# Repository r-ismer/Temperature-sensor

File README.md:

# Temperature sensor

This folder contains a hardware, a software part and a mechanical part.  
The hardware part is a KiCad project which contains the schematic and the pcb layout for the temperature and humidity sensor.  
The software part is a make project which contains all the files needed to build the firwmare that will communicate with the temperature and humidity sensor and send these inforamtion to a station (other project).  
The mechanical part is a FreeCAD project which contains the top and bottom casing for the temperature ad humidity sensor.

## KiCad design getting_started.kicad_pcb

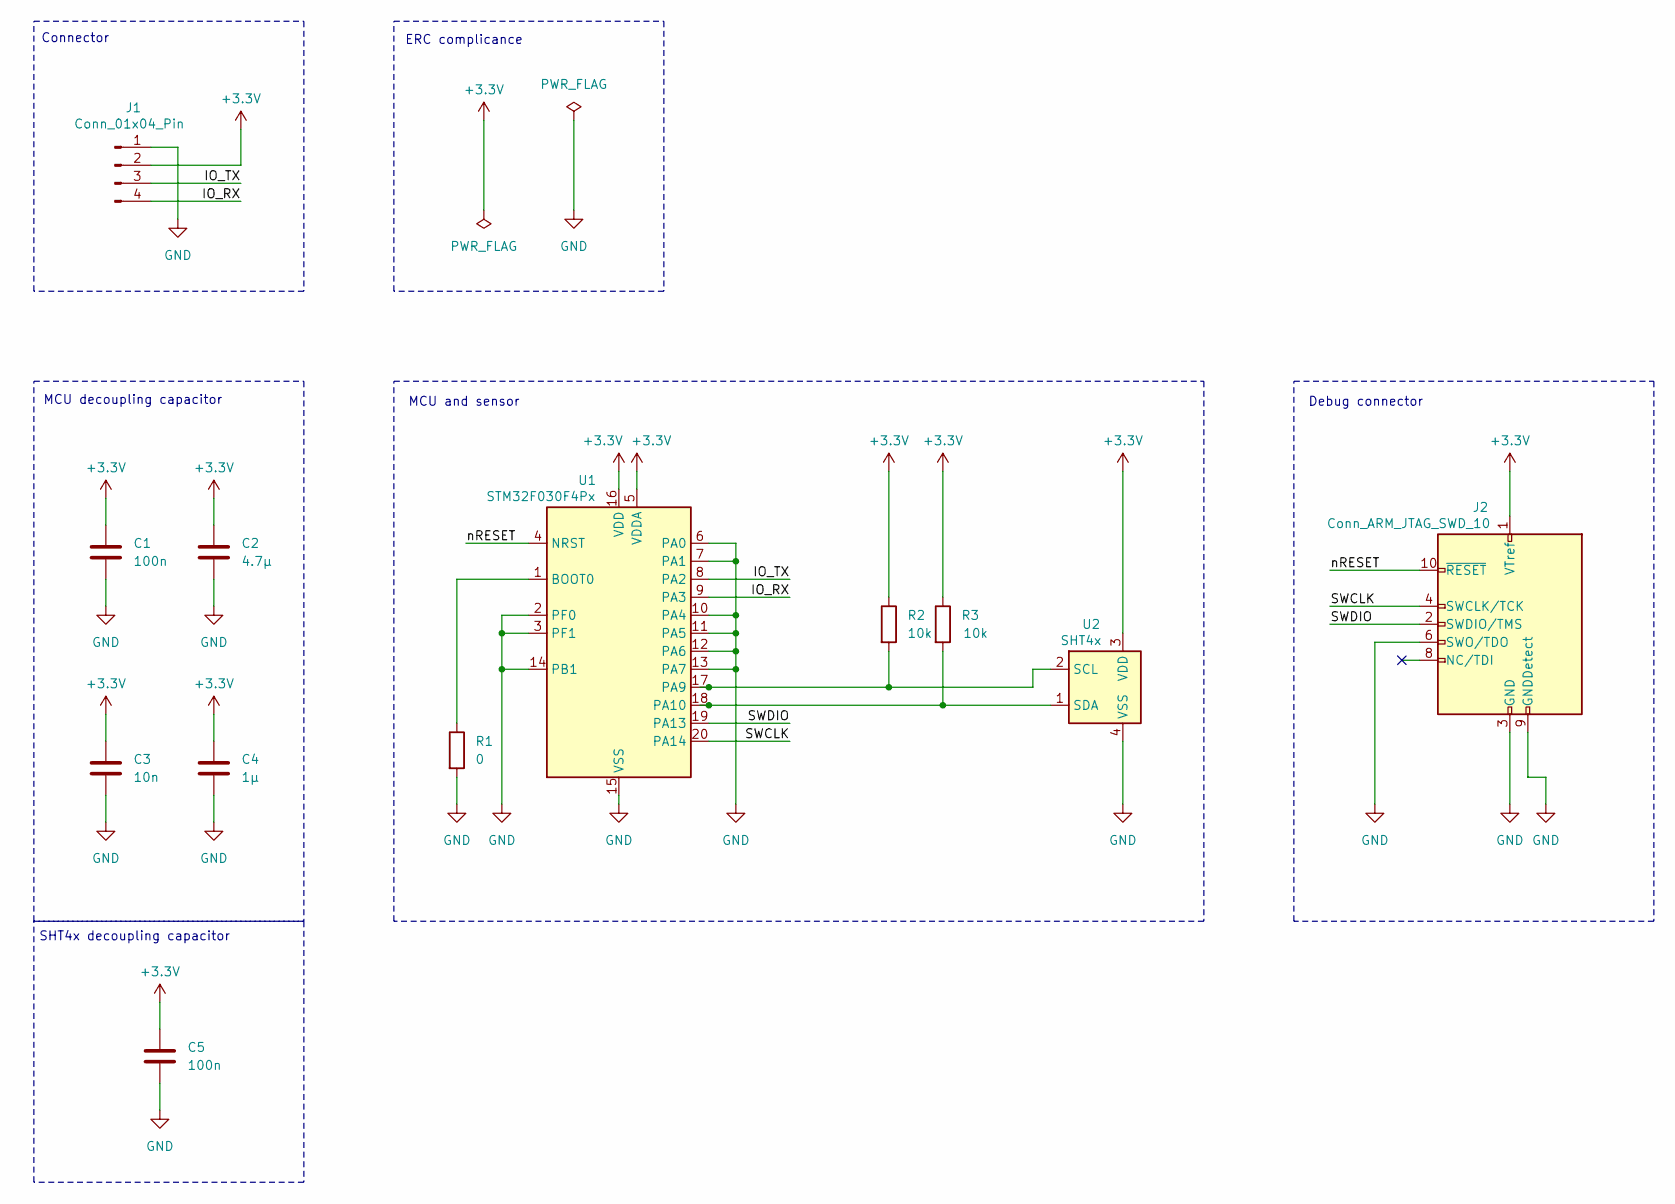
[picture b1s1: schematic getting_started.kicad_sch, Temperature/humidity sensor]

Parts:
C1, C5: 100n; C_0805_2012Metric
C2: 4.7µ; C_0805_2012Metric
C3: 10n; C_0805_2012Metric
C4: 1µ; C_0805_2012Metric
J1: Conn_01x04_Pin; JST_XA_B04B-XASK-1-A_1x04_P2.50mm_Vertical
J2: Conn_ARM_JTAG_SWD_10; PinHeader_2x05_P1.27mm_Vertical
R1: 0; R_0805_2012Metric
R2, R3: 10k; R_0805_2012Metric
U1: STM32F030F4Px; TSSOP-20_4.4x6.5mm_P0.65mm
U2: SHT4x; Sensirion_DFN-4_1.5x1.5mm_P0.8mm_SHT4x_NoCentralPad

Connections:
+3.3V: C1.1, C2.1, C3.1, C4.1, C5.1, J1.2, J2.1 (VTref), R2.1, R3.1, U1.5 (VDDA), U1.16 (VDD), U2.3 (VDD)
/IO_RX: J1.4, U1.9 (PA3)
/IO_TX: J1.3, U1.8 (PA2)
/SWCLK: J2.4 (SWCLK/TCK), U1.20 (PA14)
/SWDIO: J2.2 (SWDIO/TMS), U1.19 (PA13)
/nRESET: J2.10 (~RESET), U1.4 (NRST)
GND: C1.2, C2.2, C3.2, C4.2, C5.2, J1.1, J2.3 (GND), J2.5 (GND), J2.6 (SWO/TDO), J2.9 (GNDDetect), R1.2, U1.2 (PF0), U1.3 (PF1), U1.6 (PA0), U1.7 (PA1), U1.10 (PA4), U1.11 (PA5), U1.12 (PA6), U1.13 (PA7), U1.14 (PB1), U1.15 (VSS), U2.4 (VSS)
unnamed: R1.1, U1.1 (BOOT0)
unnamed: R2.2, U1.17 (PA9), U2.2 (SCL)
unnamed: R3.2, U1.18 (PA10), U2.1 (SDA)

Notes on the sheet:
ERC complicance
MCU decoupling capacitor
SHT4x decoupling capacitor
Connector
MCU and sensor
Debug connector

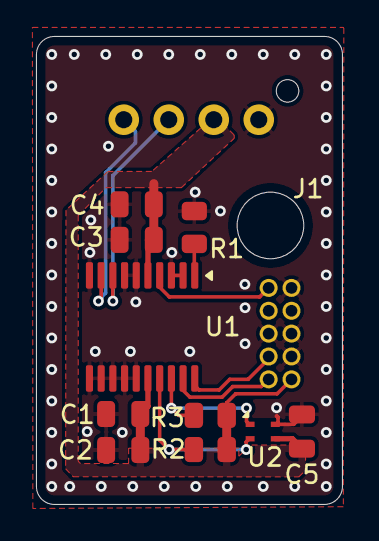
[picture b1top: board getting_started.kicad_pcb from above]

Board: 2 copper layers, 17.0 x 26.0 mm, 12 parts (0 on the bottom side), 10 nets.

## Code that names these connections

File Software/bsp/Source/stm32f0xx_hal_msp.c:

/* USER CODE BEGIN Header */
/**
  ******************************************************************************
  * @file         stm32f0xx_hal_msp.c
  * @brief        This file provides code for the MSP Initialization
  *               and de-Initialization codes.
  ******************************************************************************
  * @attention
  *
  * Copyright (c) 2026 STMicroelectronics.
  * All rights reserved.
  *
  * This software is licensed under terms that can be found in the LICENSE file
  * in the root directory of this software component.
  * If no LICENSE file comes with this software, it is provided AS-IS.
  *
  ******************************************************************************
  */
/* USER CODE END Header */

/* Includes ------------------------------------------------------------------*/
#include "main.h"
/* USER CODE BEGIN Includes */

/* USER CODE END Includes */

/* Private typedef -----------------------------------------------------------*/
/* USER CODE BEGIN TD */

/* USER CODE END TD */

/* Private define ------------------------------------------------------------*/
/* USER CODE BEGIN Define */

/* USER CODE END Define */

/* Private macro -------------------------------------------------------------*/
/* USER CODE BEGIN Macro */

/* USER CODE END Macro */

/* Private variables ---------------------------------------------------------*/
/* USER CODE BEGIN PV */

/* USER CODE END PV */

/* Private function prototypes -----------------------------------------------*/
/* USER CODE BEGIN PFP */

/* USER CODE END PFP */

/* External functions --------------------------------------------------------*/
/* USER CODE BEGIN ExternalFunctions */

/* USER CODE END ExternalFunctions */

/* USER CODE BEGIN 0 */

/* USER CODE END 0 */
/**
  * Initializes the Global MSP.
  */
void HAL_MspInit(void)
{

  /* USER CODE BEGIN MspInit 0 */

  /* USER CODE END MspInit 0 */

  __HAL_RCC_SYSCFG_CLK_ENABLE();
  __HAL_RCC_PWR_CLK_ENABLE();

  /* System interrupt init*/

  /* USER CODE BEGIN MspInit 1 */

  /* USER CODE END MspInit 1 */
}

/**
  * @brief I2C MSP Initialization
  * This function configures the hardware resources used in this example
  * @param hi2c: I2C handle pointer
  * @retval None
  */
void HAL_I2C_MspInit(I2C_HandleTypeDef* hi2c)
{
  GPIO_InitTypeDef GPIO_InitStruct = {0};
  if(hi2c->Instance==I2C1)
  {
    /* USER CODE BEGIN I2C1_MspInit 0 */

    /* USER CODE END I2C1_MspInit 0 */

    __HAL_RCC_GPIOA_CLK_ENABLE();
    /**I2C1 GPIO Configuration
    PA9     ------> I2C1_SCL
    PA10     ------> I2C1_SDA
    */
    GPIO_InitStruct.Pin = GPIO_PIN_9|GPIO_PIN_10;
    GPIO_InitStruct.Mode = GPIO_MODE_AF_OD;
    GPIO_InitStruct.Pull = GPIO_NOPULL;
    GPIO_InitStruct.Speed = GPIO_SPEED_FREQ_HIGH;
    GPIO_InitStruct.Alternate = GPIO_AF4_I2C1;
    HAL_GPIO_Init(GPIOA, &GPIO_InitStruct);

    /* Peripheral clock enable */
    __HAL_RCC_I2C1_CLK_ENABLE();
    /* USER CODE BEGIN I2C1_MspInit 1 */

    /* USER CODE END I2C1_MspInit 1 */

  }

}

/**
  * @brief I2C MSP De-Initialization
  * This function freeze the hardware resources used in this example
  * @param hi2c: I2C handle pointer
  * @retval None
  */
void HAL_I2C_MspDeInit(I2C_HandleTypeDef* hi2c)
{
  if(hi2c->Instance==I2C1)
  {
    /* USER CODE BEGIN I2C1_MspDeInit 0 */

    /* USER CODE END I2C1_MspDeInit 0 */
    /* Peripheral clock disable */
    __HAL_RCC_I2C1_CLK_DISABLE();

    /**I2C1 GPIO Configuration
    PA9     ------> I2C1_SCL
    PA10     ------> I2C1_SDA
    */
    HAL_GPIO_DeInit(GPIOA, GPIO_PIN_9);

    HAL_GPIO_DeInit(GPIOA, GPIO_PIN_10);

    /* USER CODE BEGIN I2C1_MspDeInit 1 */

    /* USER CODE END I2C1_MspDeInit 1 */
  }

}

/**
  * @brief UART MSP Initialization
  * This function configures the hardware resources used in this example
  * @param huart: UART handle pointer
  * @retval None
  */
void HAL_UART_MspInit(UART_HandleTypeDef* huart)
{
  GPIO_InitTypeDef GPIO_InitStruct = {0};
  if(huart->Instance==USART1)
  {
    /* USER CODE BEGIN USART1_MspInit 0 */

    /* USER CODE END USART1_MspInit 0 */
    /* Peripheral clock enable */
    __HAL_RCC_USART1_CLK_ENABLE();

    __HAL_RCC_GPIOA_CLK_ENABLE();
    /**USART1 GPIO Configuration
    PA2     ------> USART1_TX
    PA3     ------> USART1_RX
    */
    GPIO_InitStruct.Pin = GPIO_PIN_2|GPIO_PIN_3;
    GPIO_InitStruct.Mode = GPIO_MODE_AF_PP;
    GPIO_InitStruct.Pull = GPIO_NOPULL;
    GPIO_InitStruct.Speed = GPIO_SPEED_FREQ_HIGH;
    GPIO_InitStruct.Alternate = GPIO_AF1_USART1;
    HAL_GPIO_Init(GPIOA, &GPIO_InitStruct);

    /* USER CODE BEGIN USART1_MspInit 1 */

    /* USER CODE END USART1_MspInit 1 */

  }

}

/**
  * @brief UART MSP De-Initialization
  * This function freeze the hardware resources used in this example
  * @param huart: UART handle pointer
  * @retval None
  */
void HAL_UART_MspDeInit(UART_HandleTypeDef* huart)
{
  if(huart->Instance==USART1)
  {
    /* USER CODE BEGIN USART1_MspDeInit 0 */

    /* USER CODE END USART1_MspDeInit 0 */
    /* Peripheral clock disable */
    __HAL_RCC_USART1_CLK_DISABLE();

    /**USART1 GPIO Configuration
    PA2     ------> USART1_TX
    PA3     ------> USART1_RX
    */
    HAL_GPIO_DeInit(GPIOA, GPIO_PIN_2|GPIO_PIN_3);

    /* USER CODE BEGIN USART1_MspDeInit 1 */

    /* USER CODE END USART1_MspDeInit 1 */
  }

}

/* USER CODE BEGIN 1 */

/* USER CODE END 1 */

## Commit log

2026-01-02 first commmit
2026-01-02 Changed debug connector footprint
2026-01-02 Updated JST connector
2026-01-03 Updated gitignore
2026-01-05 Updated schematic and pcb
2026-01-06 Added power plane
2026-01-08 Updated planes
2026-01-08 Pass ERC and DRC
2026-01-10 Updated pcb layout
2026-01-17 Updated 3D image of board
2026-01-27 Split hardware and software
2026-01-28 Initial commit for software part
2026-01-29 Tested temperature and humidity sensor
2026-01-30 Cleaned code
2026-01-30 Created driver for SHT4x
2026-02-01 Updated makefile
2026-02-06 Added task
2026-02-08 Added wait for interrupt
2026-02-14 Added files for casing
2026-02-14 Added mechanical part to the main README
2026-02-18 Updated top casing
2026-03-01 Updated top and bottom mechanical parts
2026-03-14 Improved mechanical top and bottom parts
2026-03-21 Reworked bottom and top casing after first print
2026-06-02 Updated casing for more strenght
